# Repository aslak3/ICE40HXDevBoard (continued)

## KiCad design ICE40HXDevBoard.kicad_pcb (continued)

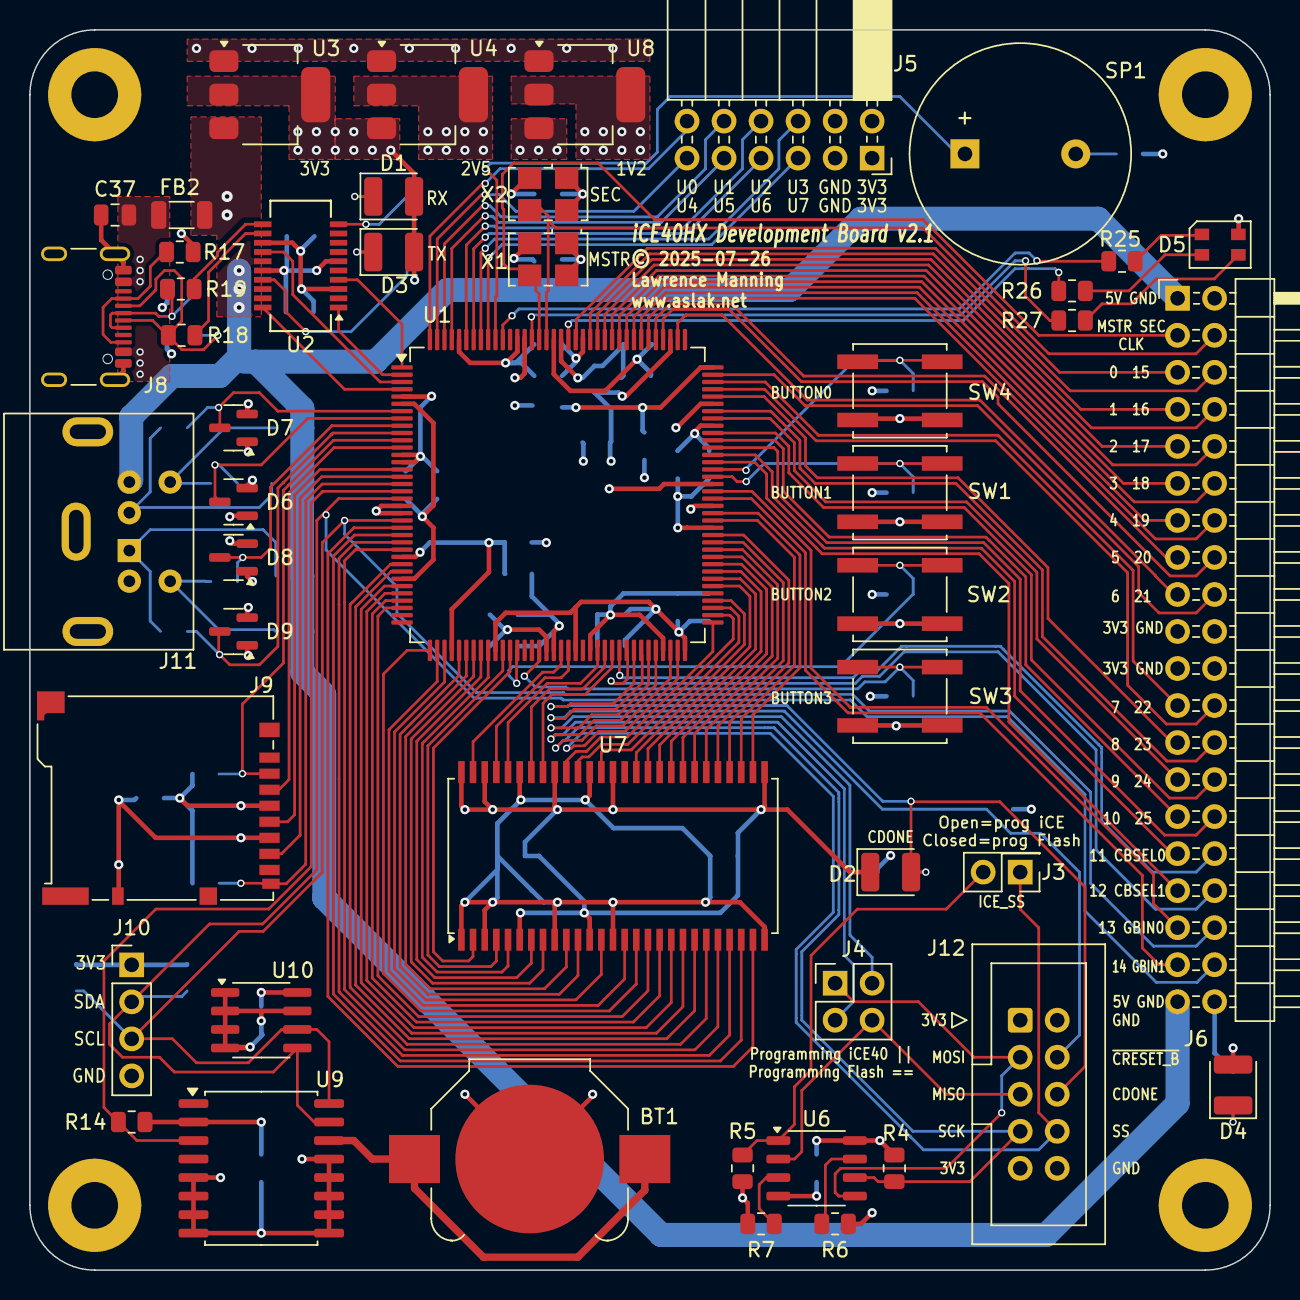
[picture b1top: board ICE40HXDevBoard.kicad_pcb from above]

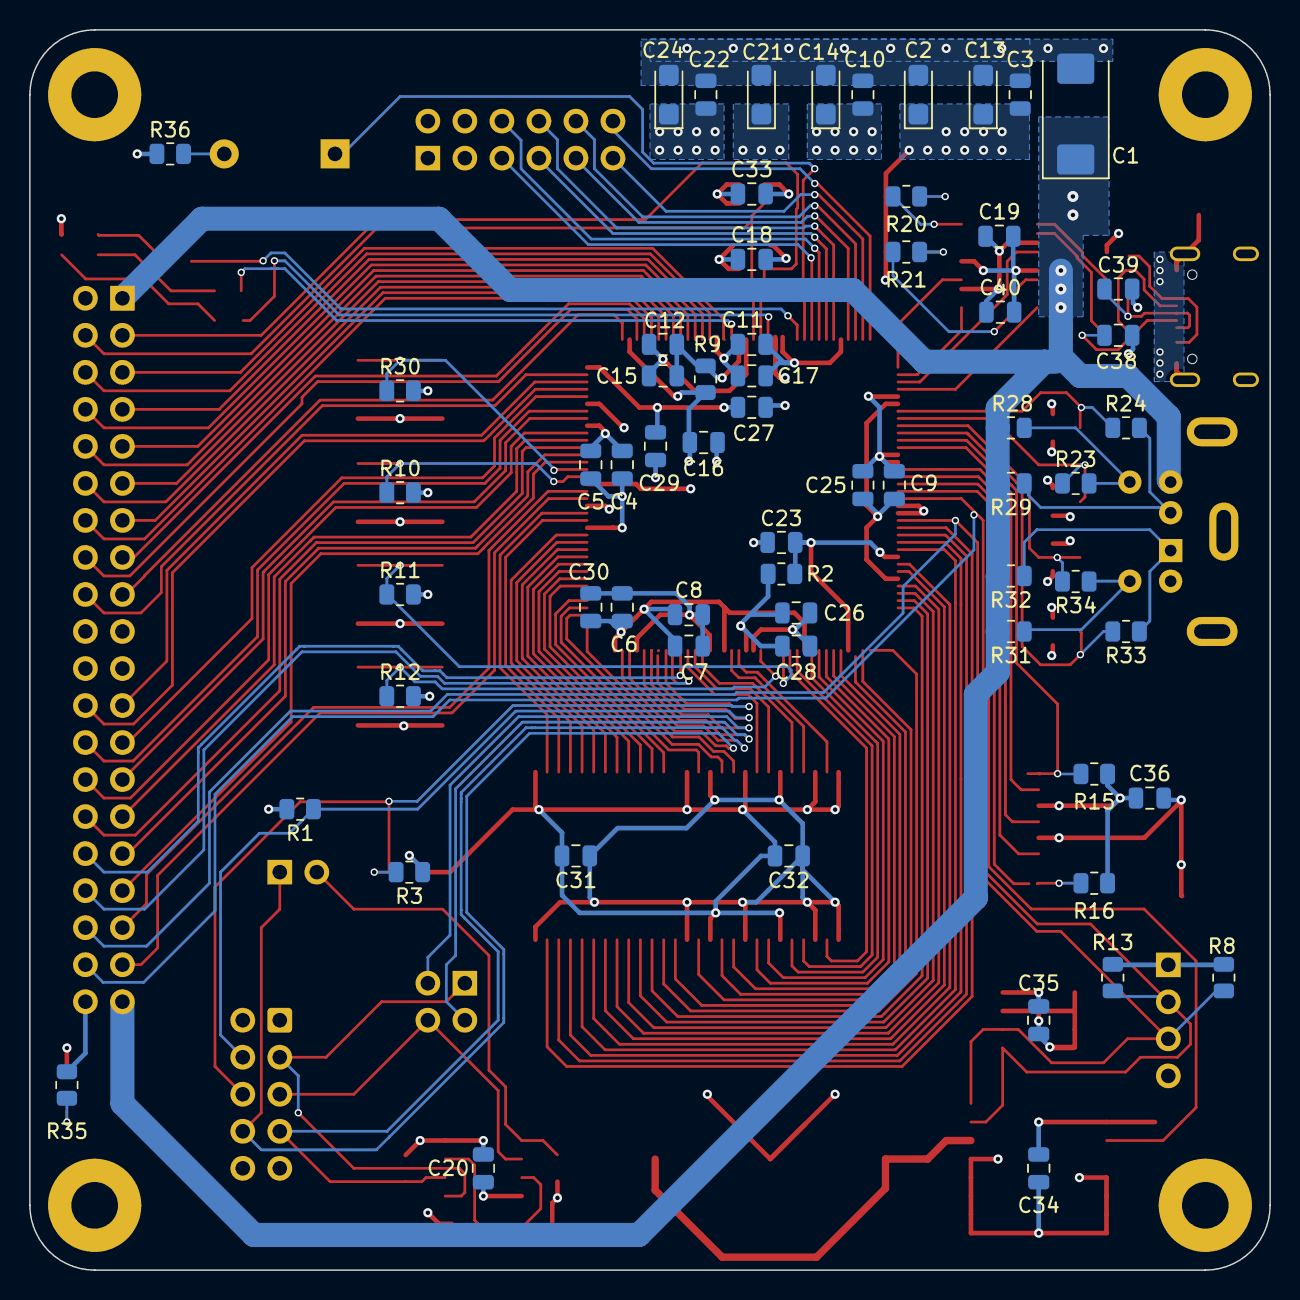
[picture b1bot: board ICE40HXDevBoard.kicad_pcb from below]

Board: 4 copper layers, 85.1 x 85.1 mm, 115 parts (63 on the bottom side), 141 nets.

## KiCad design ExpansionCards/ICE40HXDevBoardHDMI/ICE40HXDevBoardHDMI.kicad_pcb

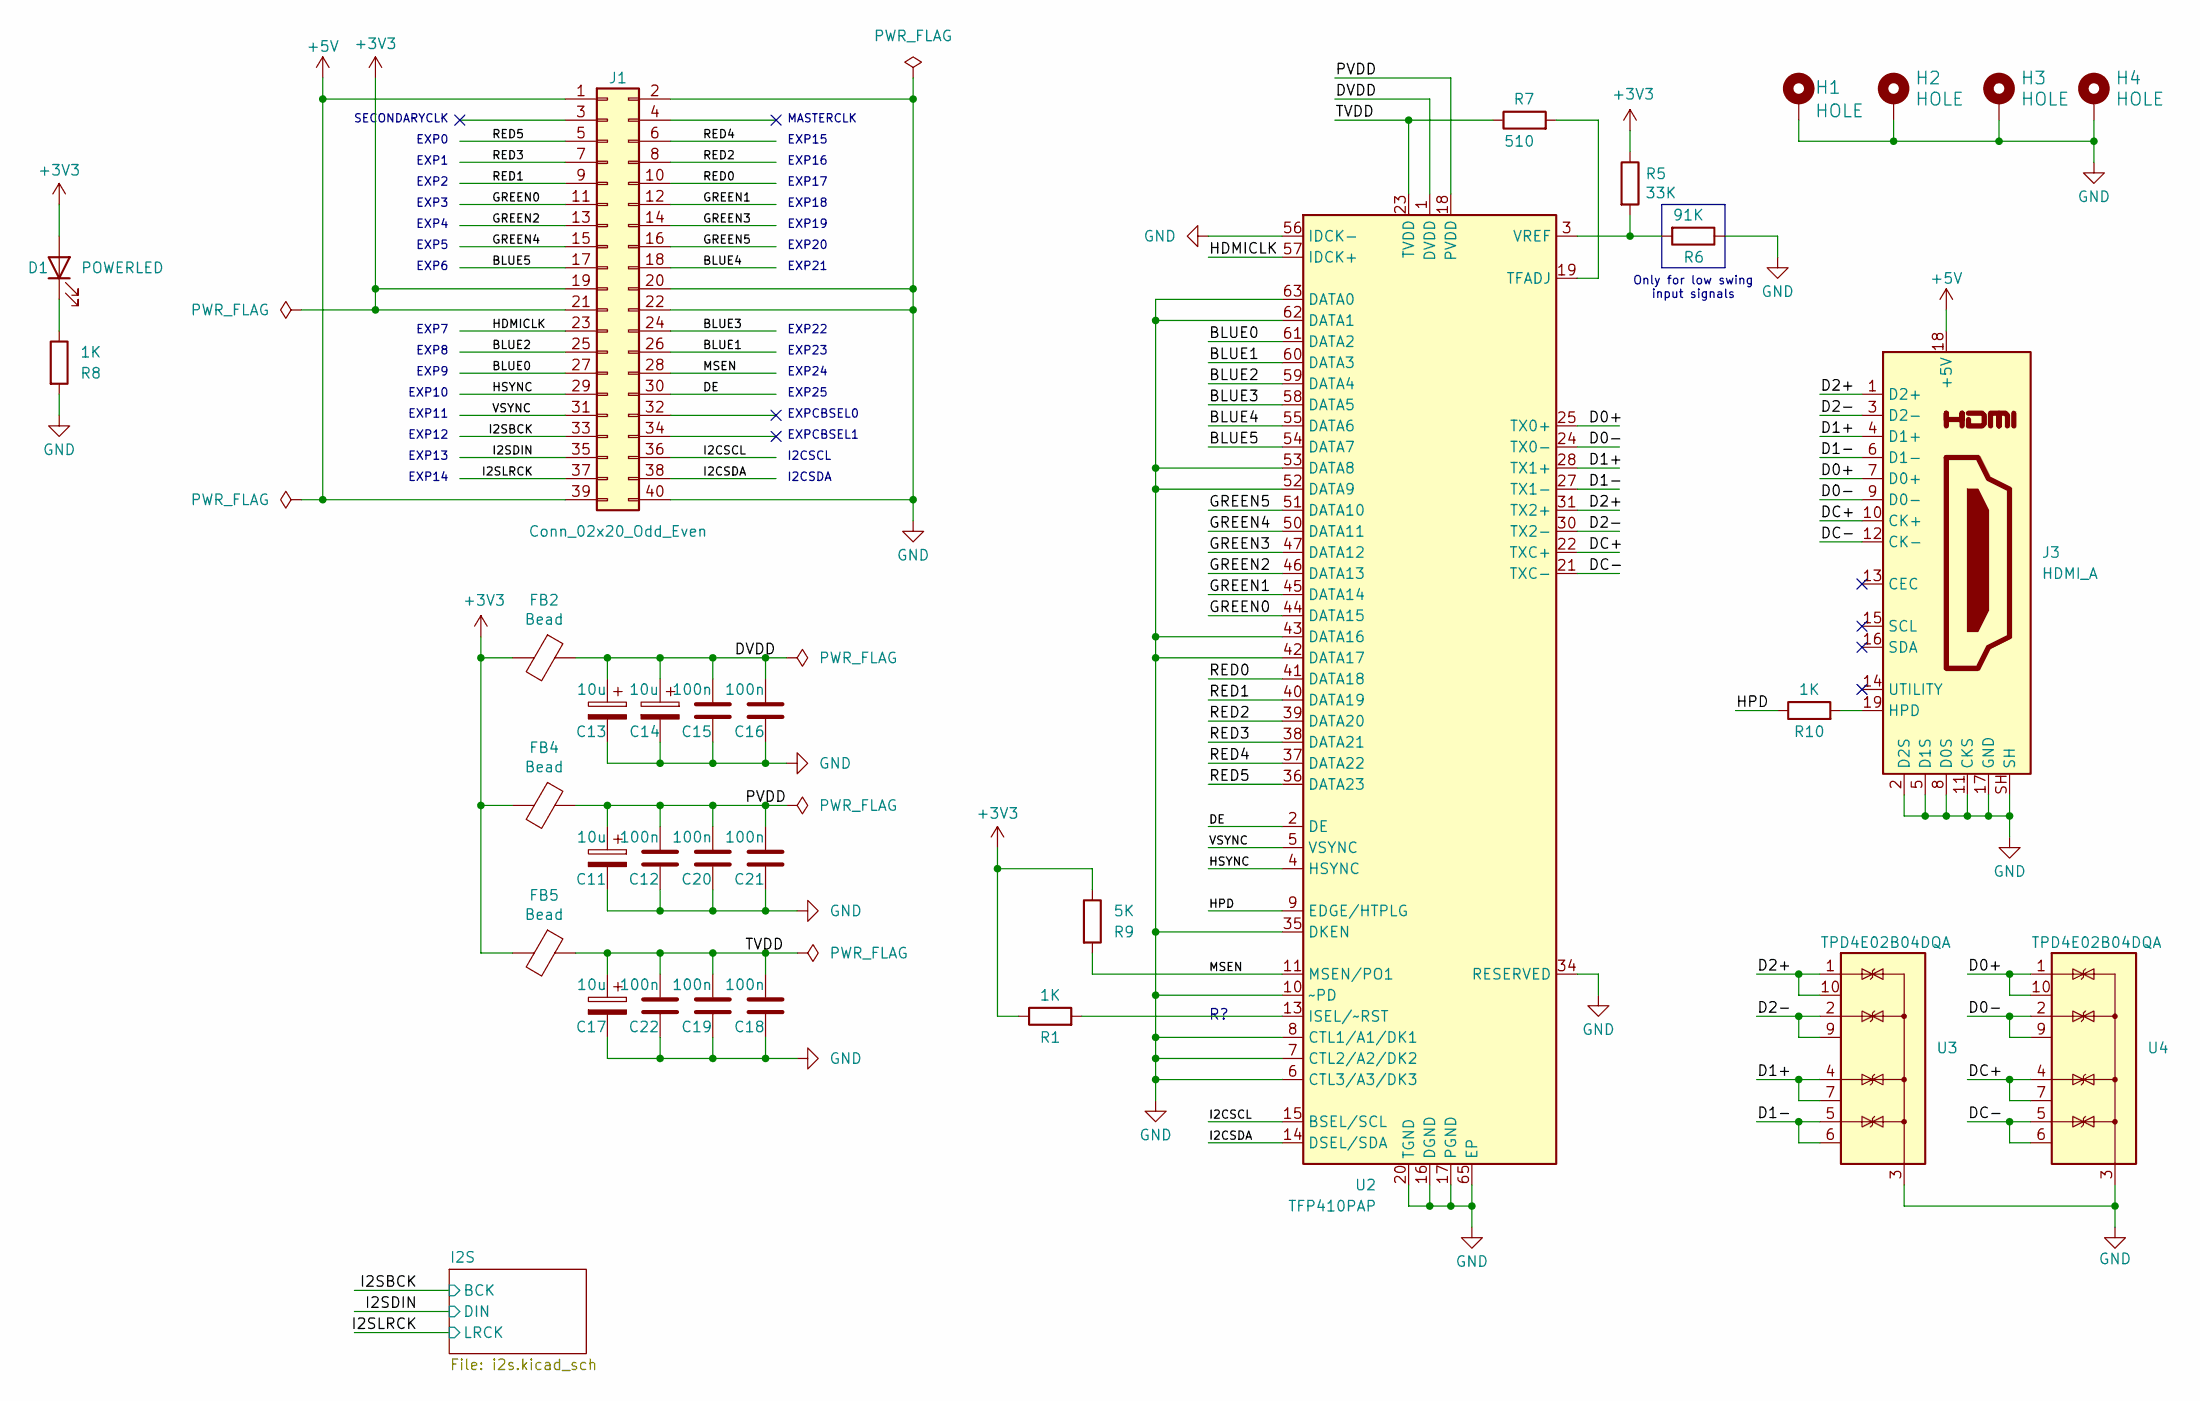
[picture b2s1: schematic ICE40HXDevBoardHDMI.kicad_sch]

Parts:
C11, C13, C14, C17: 10u; CP_EIA-3216-18_Kemet-A
C12, C15, C16, C18, C19, C20, C21, C22: 100n; C_0603_1608Metric
D1: POWERLED; LED_1210_3225Metric
FB2, FB4, FB5: Bead; L_0805_2012Metric
H1, H2, H3, H4: HOLE; MountingHole_3.2mm_M3_Pad
J1: Conn_02x20_Odd_Even; PinSocket_2x20_P2.54mm_Horizontal
J3: HDMI_A; HDMI_A_Molex_208658-1001_Horizontal
R1, R8, R10: 1K; R_0805_2012Metric
R5: 33K; R_0805_2012Metric
R6: 91K; R_0805_2012Metric
R7: 510; R_0805_2012Metric
R9: 5K; R_0805_2012Metric
U2: TFP410PAP; LQFP-64-1EP_10x10mm_P0.5mm_EP5x5mm_ThermalVias; MPN TFP410PAP; LCSC Part # C1543847
U3, U4: TPD4E02B04DQA; USON-10_2.5x1.0mm_P0.5mm

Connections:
+3V3: D1.2 (A), FB2.2, FB4.2, FB5.2, J1.19, J1.21, R1.1, R5.1, R9.1; also elsewhere on the board
+5V: J1.1, J1.39, J3.18 (+5V)
/BLUE0: J1.27, U2.61 (DATA2)
/BLUE1: J1.26, U2.60 (DATA3)
/BLUE2: J1.25, U2.59 (DATA4)
/BLUE3: J1.24, U2.58 (DATA5)
/BLUE4: J1.18, U2.55 (DATA6)
/BLUE5: J1.17, U2.54 (DATA7)
/D0+: J3.7 (D0+), U2.25 (TX0+), U4.1 (IO1), U4.10 (NC)
/D0-: J3.9 (D0-), U2.24 (TX0-), U4.2 (IO2), U4.9 (NC)
/D1+: J3.4 (D1+), U2.28 (TX1+), U3.4 (IO3), U3.7 (NC)
/D1-: J3.6 (D1-), U2.27 (TX1-), U3.5 (IO4), U3.6 (NC)
/D2+: J3.1 (D2+), U2.31 (TX2+), U3.1 (IO1), U3.10 (NC)
/D2-: J3.3 (D2-), U2.30 (TX2-), U3.2 (IO2), U3.9 (NC)
/DC+: J3.10 (CK+), U2.22 (TXC+), U4.4 (IO3), U4.7 (NC)
/DC-: J3.12 (CK-), U2.21 (TXC-), U4.5 (IO4), U4.6 (NC)
/DE: J1.30, U2.2 (DE)
/DVDD: C13.1, C14.1, C15.1, C16.1, FB2.1, U2.1 (DVDD), U2.12 (DVDD), U2.33 (DVDD)
/GREEN0: J1.11, U2.44 (DATA15)
/GREEN1: J1.12, U2.45 (DATA14)
/GREEN2: J1.13, U2.46 (DATA13)
/GREEN3: J1.14, U2.47 (DATA12)
/GREEN4: J1.15, U2.50 (DATA11)
/GREEN5: J1.16, U2.51 (DATA10)
/HDMICLK: J1.23, U2.57 (IDCK+)
/HPD: R10.1, U2.9 (EDGE/HTPLG)
/HSYNC: J1.29, U2.4 (HSYNC)
/I2CSCL: J1.36, U2.15 (BSEL/SCL)
/I2CSDA: J1.38, U2.14 (DSEL/SDA)
/I2SBCK: J1.33; also elsewhere on the board
/I2SDIN: J1.35; also elsewhere on the board
/I2SLRCK: J1.37; also elsewhere on the board
/MSEN: J1.28, R9.2, U2.11 (MSEN/PO1)
/PVDD: C11.1, C12.1, C20.1, C21.1, FB4.1, U2.18 (PVDD)
/RED0: J1.10, U2.41 (DATA18)
/RED1: J1.9, U2.40 (DATA19)
/RED2: J1.8, U2.39 (DATA20)
/RED3: J1.7, U2.38 (DATA21)
/RED4: J1.6, U2.37 (DATA22)
/RED5: J1.5, U2.36 (DATA23)
/TVDD: C17.1, C18.1, C19.1, C22.1, FB5.1, R7.1, U2.23 (TVDD), U2.29 (TVDD)
/VSYNC: J1.31, U2.5 (VSYNC)
GND: C11.2, C12.2, C13.2, C14.2, C15.2, C16.2, C17.2, C18.2, C19.2, C20.2, C21.2, C22.2, H1.1, H2.1, H3.1, H4.1, J1.2, J1.20, J1.22, J1.40, J3.2 (D2S), J3.5 (D1S), J3.8 (D0S), J3.11 (CKS), J3.17 (GND), J3.SH, R6.1, R8.2, U2.6 (CTL3/A3/DK3), U2.7 (CTL2/A2/DK2), U2.8 (CTL1/A1/DK1), U2.10 (~PD), U2.16 (DGND), U2.17 (PGND), U2.20 (TGND), U2.26 (TGND), U2.32 (TGND), U2.34 (RESERVED), U2.35 (DKEN), U2.42 (DATA17), U2.43 (DATA16), U2.48 (DGND), U2.52 (DATA9), U2.53 (DATA8), U2.56 (IDCK-), U2.62 (DATA1), U2.63 (DATA0), U2.64 (DGND), U2.65 (EP), U3.3 (G), U3.8 (G), U4.3 (G), U4.8 (G); also elsewhere on the board
unnamed: D1.1 (K), R8.1
unnamed: J3.19 (HPD), R10.2
unnamed: R1.2, U2.13 (ISEL/~RST)
unnamed: R7.2, U2.19 (TFADJ)
unnamed: R5.2, R6.2, U2.3 (VREF)

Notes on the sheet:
EXP13
EXP8
EXP24
EXP16
EXP4
EXP3
EXP14
EXP20
EXP23
EXP22
EXP5
Only for low swing input signals
EXP1
I2CSDA
EXP6
EXP2
EXP0
SECONDARYCLK
EXP25
MASTERCLK
EXP11
EXP9
EXP10
EXPCBSEL0
EXP15
EXP17
EXP19
EXPCBSEL1
EXP7
I2CSCL
EXP12
EXP18
EXP21

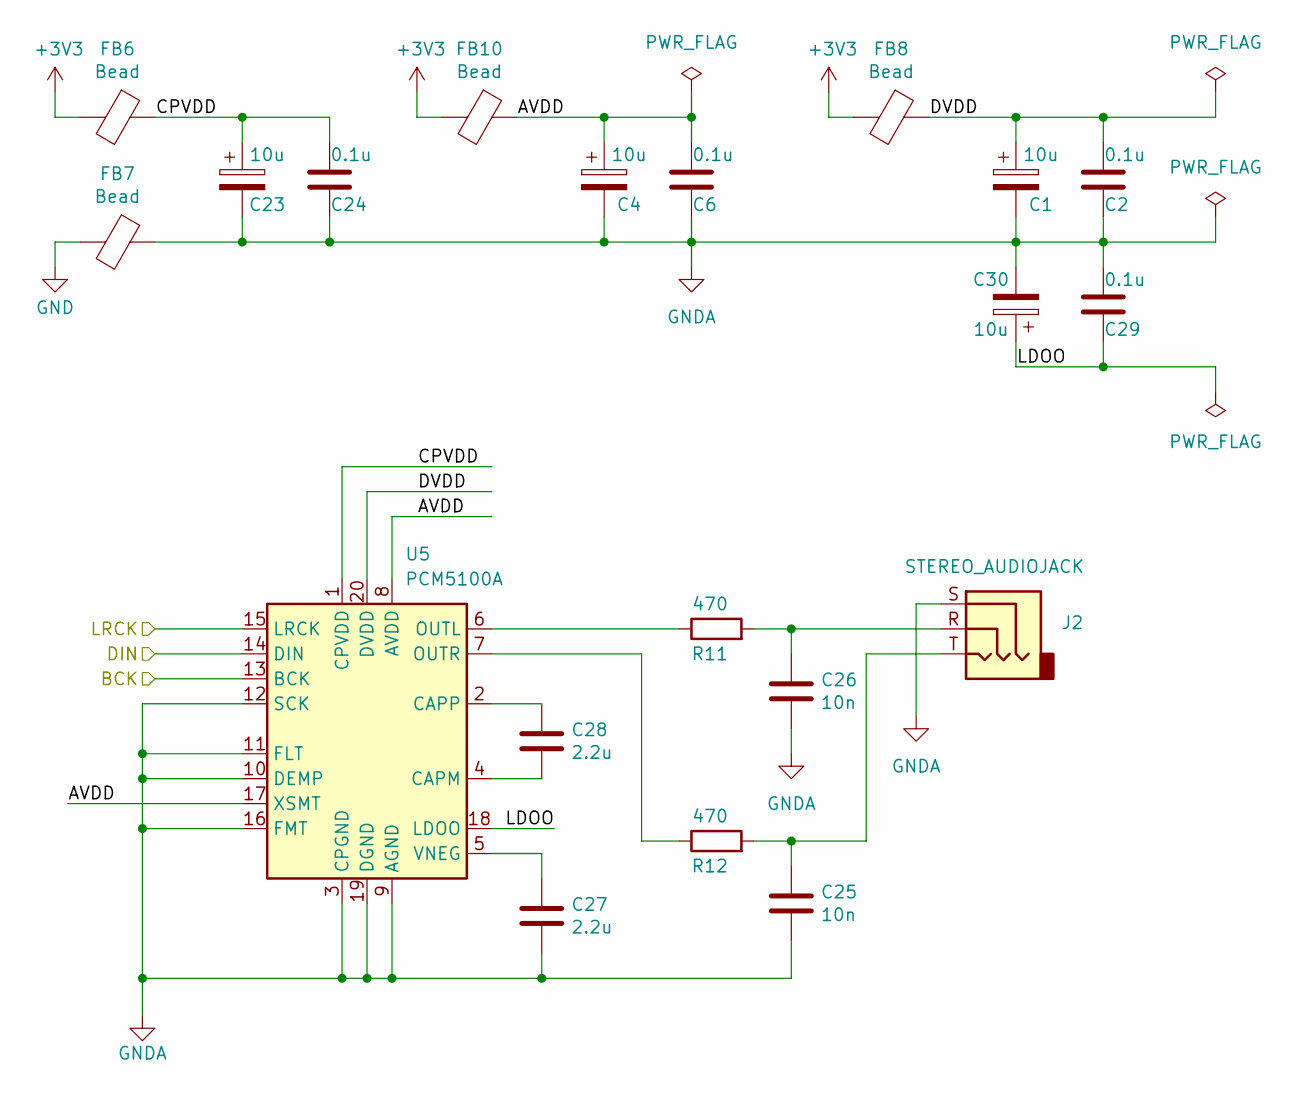
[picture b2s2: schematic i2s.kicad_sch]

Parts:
C1, C4, C23, C30: 10u; CP_EIA-3216-18_Kemet-A
C2, C6, C24, C29: 0.1u; C_0805_2012Metric
C25, C26: 10n; C_0805_2012Metric
C27, C28: 2.2u; C_0805_2012Metric
FB6, FB7, FB8, FB10: Bead; L_1206_3216Metric
J2: STEREO_AUDIOJACK; Jack_3.5mm_Switronic_ST-005-G_horizontal
R11, R12: 470; R_0805_2012Metric
U5: PCM5100A; TSSOP-20_4.4x6.5mm_P0.65mm

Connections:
+3V3: FB6.2, FB8.2, FB10.2; also elsewhere on the board
/I2S/AVDD: C4.1, C6.1, FB10.1, U5.8 (AVDD), U5.17 (XSMT)
/I2S/CPVDD: C23.1, C24.1, FB6.1, U5.1 (CPVDD)
/I2S/DVDD: C1.1, C2.1, FB8.1, U5.20 (DVDD)
/I2S/LDOO: C29.2, C30.1, U5.18 (LDOO)
/I2SBCK: U5.13 (BCK); also elsewhere on the board
/I2SDIN: U5.14 (DIN); also elsewhere on the board
/I2SLRCK: U5.15 (LRCK); also elsewhere on the board
GND: FB7.2; also elsewhere on the board
GNDA: C1.2, C2.2, C4.2, C6.2, C23.2, C24.2, C25.2, C26.2, C27.2, C29.1, C30.2, FB7.1, J2.S, U5.3 (CPGND), U5.9 (AGND), U5.10 (DEMP), U5.11 (FLT), U5.12 (SCK), U5.16 (FMT), U5.19 (DGND)
unnamed: C25.1, J2.T, R12.2
unnamed: C26.1, J2.R, R11.2
unnamed: C28.2, U5.4 (CAPM)
unnamed: C28.1, U5.2 (CAPP)
unnamed: R11.1, U5.6 (OUTL)
unnamed: R12.1, U5.7 (OUTR)
unnamed: C27.1, U5.5 (VNEG)

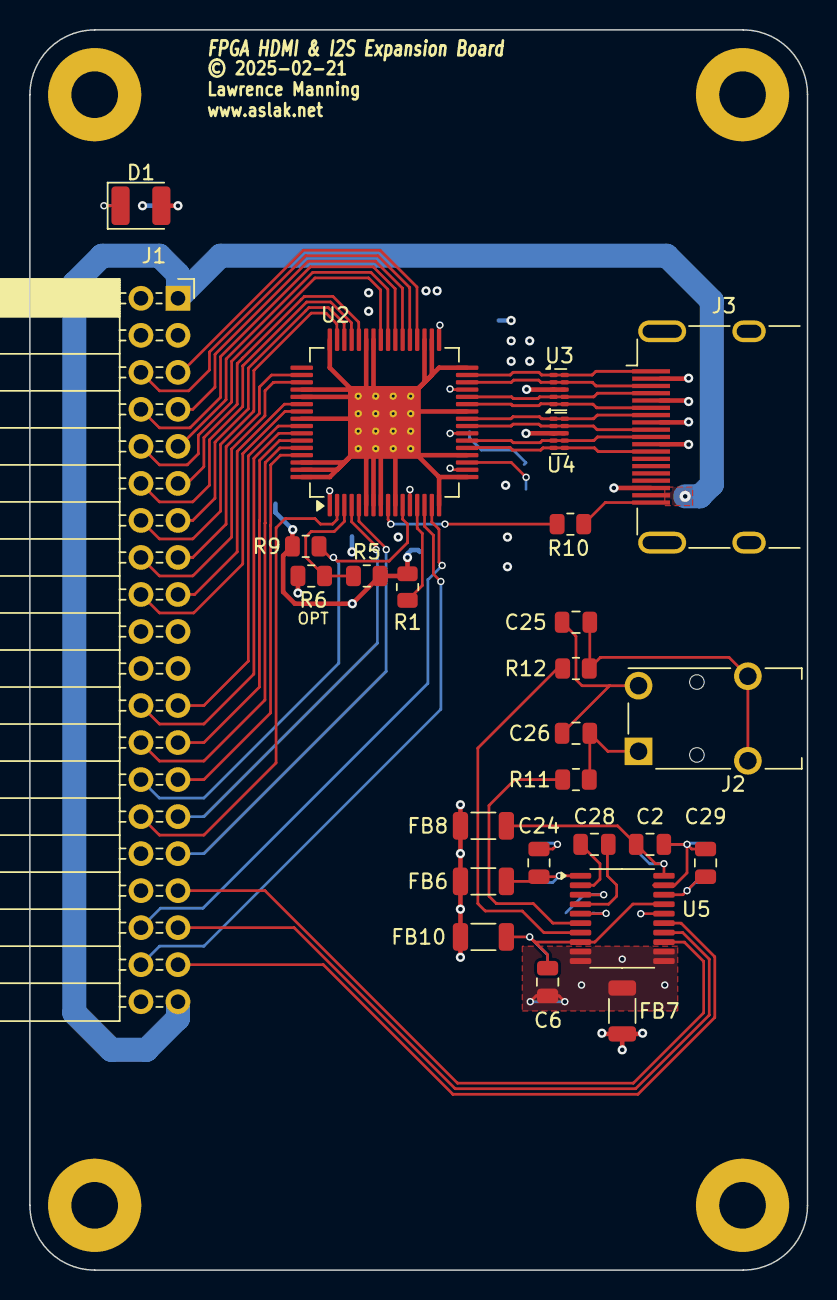
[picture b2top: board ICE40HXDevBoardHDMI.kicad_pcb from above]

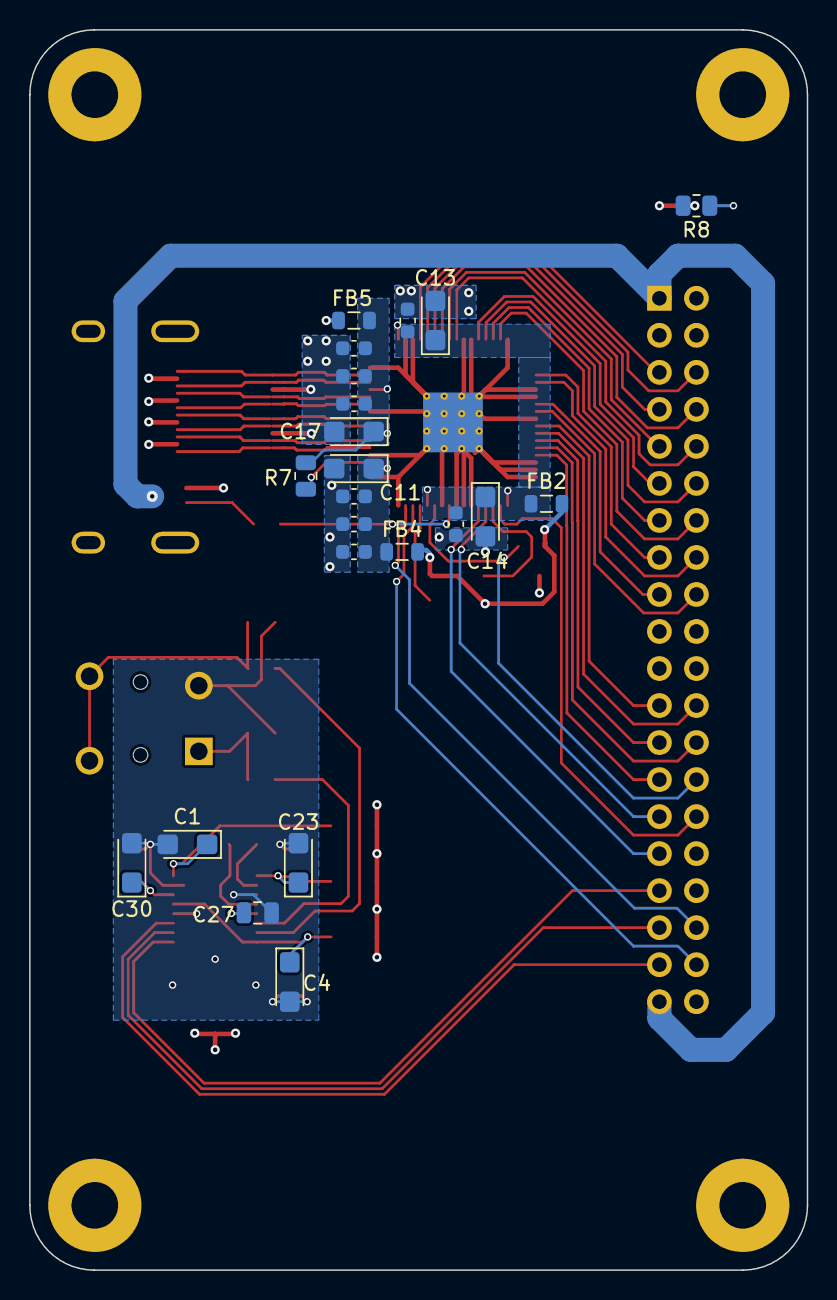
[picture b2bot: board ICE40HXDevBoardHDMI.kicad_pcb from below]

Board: 4 copper layers, 53.4 x 85.1 mm, 52 parts (22 on the bottom side), 60 nets.

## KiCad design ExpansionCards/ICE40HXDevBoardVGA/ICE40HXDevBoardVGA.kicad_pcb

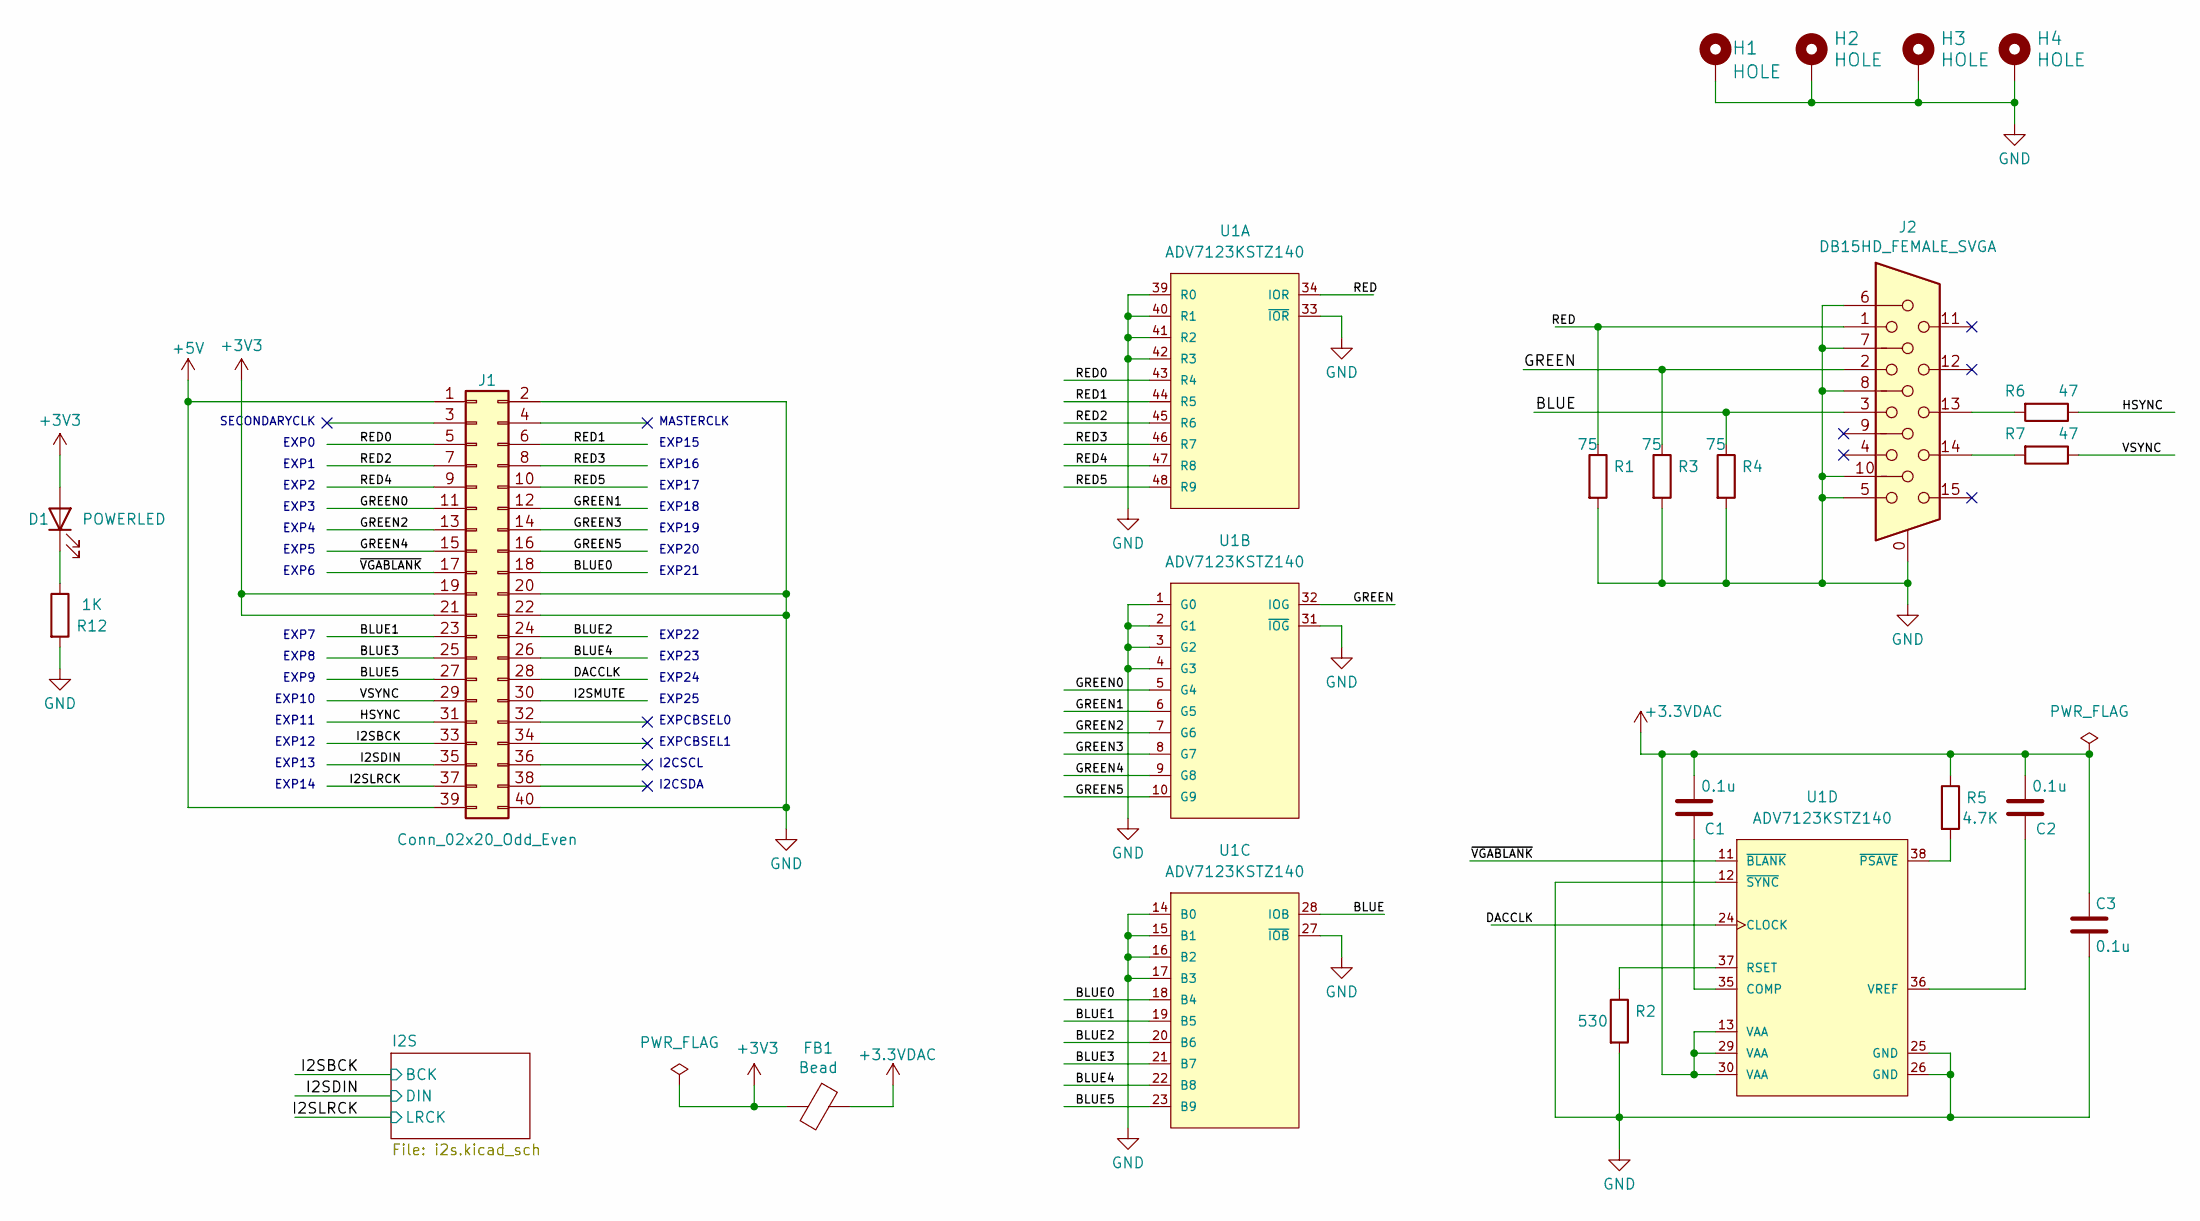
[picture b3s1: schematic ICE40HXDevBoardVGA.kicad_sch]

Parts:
C1, C2, C3: 0.1u; C_0805_2012Metric
D1: POWERLED; LED_1210_3225Metric
FB1: Bead; L_1206_3216Metric
H1, H2, H3, H4: HOLE; MountingHole_3.2mm_M3_Pad
J1: Conn_02x20_Odd_Even; PinSocket_2x20_P2.54mm_Horizontal
J2: DB15HD_FEMALE_SVGA; DSUB-15-HD_Female_Horizontal_P2.29x1.90mm_EdgePinOffset3.03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
R1, R3, R4: 75; R_0805_2012Metric
R2: 530; R_0805_2012Metric
R5: 4.7K; R_0805_2012Metric
R6, R7: 47; R_0805_2012Metric
R12: 1K; R_0805_2012Metric
U1: ADV7123KSTZ140; LQFP-48_7x7mm_P0.5mm

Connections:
+3.3VDAC: C1.2, C2.2, C3.1, FB1.1, R5.1, U1.13 (VAA), U1.29 (VAA), U1.30 (VAA)
+3V3: D1.2 (A), FB1.2, J1.19, J1.21; also elsewhere on the board
+5V: J1.1, J1.39
/BLUE: J2.3, R4.1, U1.28 (IOB)
/BLUE0: J1.18, U1.18 (B4)
/BLUE1: J1.23, U1.19 (B5)
/BLUE2: J1.24, U1.20 (B6)
/BLUE3: J1.25, U1.21 (B7)
/BLUE4: J1.26, U1.22 (B8)
/BLUE5: J1.27, U1.23 (B9)
/DACCLK: J1.28, U1.24 (CLOCK)
/GREEN: J2.2, R3.1, U1.32 (IOG)
/GREEN0: J1.11, U1.5 (G4)
/GREEN1: J1.12, U1.6 (G5)
/GREEN2: J1.13, U1.7 (G6)
/GREEN3: J1.14, U1.8 (G7)
/GREEN4: J1.15, U1.9 (G8)
/GREEN5: J1.16, U1.10 (G9)
/HSYNC: J1.31, R6.1
/I2SBCK: J1.33; also elsewhere on the board
/I2SDIN: J1.35; also elsewhere on the board
/I2SLRCK: J1.37; also elsewhere on the board
/I2SMUTE: J1.30
/RED: J2.1, R1.1, U1.34 (IOR)
/RED0: J1.5, U1.43 (R4)
/RED1: J1.6, U1.44 (R5)
/RED2: J1.7, U1.45 (R6)
/RED3: J1.8, U1.46 (R7)
/RED4: J1.9, U1.47 (R8)
/RED5: J1.10, U1.48 (R9)
/VSYNC: J1.29, R7.1
/~VGABLANK: J1.17, U1.11 (~BLANK)
GND: C3.2, H1.1, H2.1, H3.1, H4.1, J1.2, J1.20, J1.22, J1.40, J2.0, J2.5, J2.6, J2.7, J2.8, J2.10, R1.2, R2.2, R3.2, R4.2, R12.2, U1.1 (G0), U1.2 (G1), U1.3 (G2), U1.4 (G3), U1.12 (~SYNC), U1.14 (B0), U1.15 (B1), U1.16 (B2), U1.17 (B3), U1.25 (GND), U1.26 (GND), U1.27 (~IOB), U1.31 (~IOG), U1.33 (~IOR), U1.39 (R0), U1.40 (R1), U1.41 (R2), U1.42 (R3); also elsewhere on the board
unnamed: D1.1 (K), R12.1
unnamed: J2.13, R6.2
unnamed: J2.14, R7.2
unnamed: C1.1, U1.35 (COMP)
unnamed: R2.1, U1.37 (RSET)
unnamed: C2.1, U1.36 (VREF)
unnamed: R5.2, U1.38 (~PSAVE)

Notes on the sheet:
EXP13
EXP8
EXP24
EXP16
EXP4
EXP3
EXP14
EXP20
EXP23
EXP22
EXP5
EXP1
I2CSDA
EXP6
EXP2
EXP0
SECONDARYCLK
EXP25
MASTERCLK
EXP11
EXP9
EXP10
EXPCBSEL0
EXP15
EXP17
EXP19
EXPCBSEL1
EXP7
I2CSCL
EXP12
EXP18
EXP21

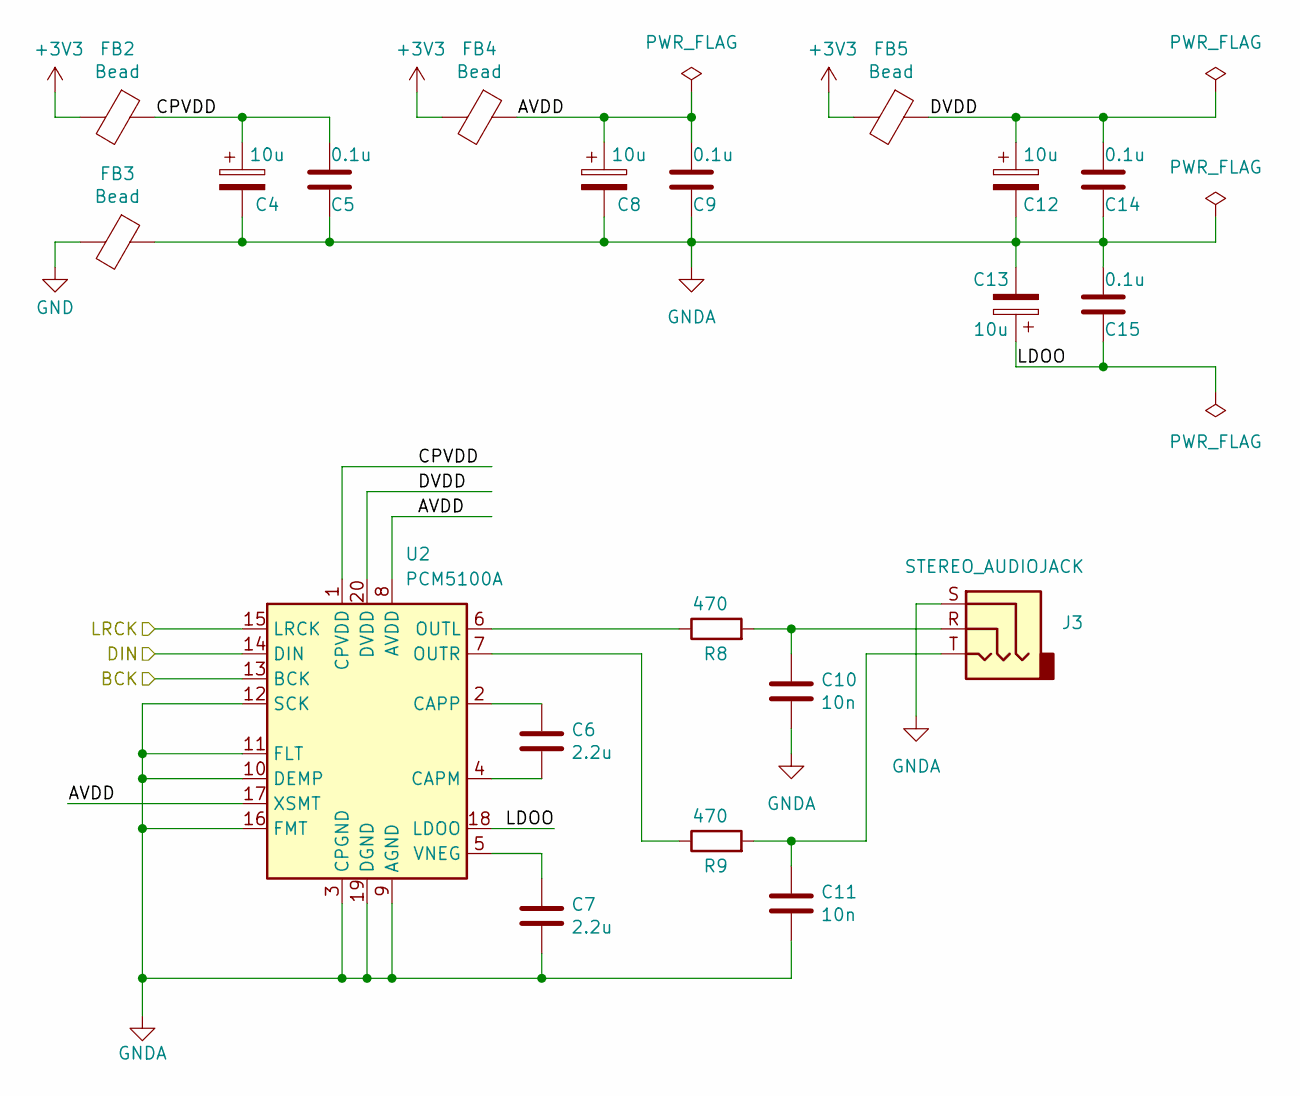
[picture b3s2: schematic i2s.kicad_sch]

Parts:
C4, C8, C12, C13: 10u; CP_EIA-3216-18_Kemet-A
C5, C9, C14, C15: 0.1u; C_0805_2012Metric
C6, C7: 2.2u; C_0805_2012Metric
C10, C11: 10n; C_0805_2012Metric
FB2, FB3, FB4, FB5: Bead; L_1206_3216Metric
J3: STEREO_AUDIOJACK; Jack_3.5mm_Switronic_ST-005-G_horizontal
R8, R9: 470; R_0805_2012Metric
U2: PCM5100A; TSSOP-20_4.4x6.5mm_P0.65mm

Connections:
+3V3: FB2.2, FB4.2, FB5.2; also elsewhere on the board
/I2S/AVDD: C8.1, C9.1, FB4.1, U2.8 (AVDD), U2.17 (XSMT)
/I2S/CPVDD: C4.1, C5.1, FB2.1, U2.1 (CPVDD)
/I2S/DVDD: C12.1, C14.1, FB5.1, U2.20 (DVDD)
/I2S/LDOO: C13.1, C15.2, U2.18 (LDOO)
/I2SBCK: U2.13 (BCK); also elsewhere on the board
/I2SDIN: U2.14 (DIN); also elsewhere on the board
/I2SLRCK: U2.15 (LRCK); also elsewhere on the board
GND: FB3.2; also elsewhere on the board
GNDA: C4.2, C5.2, C7.2, C8.2, C9.2, C10.2, C11.2, C12.2, C13.2, C14.2, C15.1, FB3.1, J3.S, U2.3 (CPGND), U2.9 (AGND), U2.10 (DEMP), U2.11 (FLT), U2.12 (SCK), U2.16 (FMT), U2.19 (DGND)
unnamed: C10.1, J3.R, R8.2
unnamed: C11.1, J3.T, R9.2
unnamed: C6.2, U2.4 (CAPM)
unnamed: C6.1, U2.2 (CAPP)
unnamed: R8.1, U2.6 (OUTL)
unnamed: R9.1, U2.7 (OUTR)
unnamed: C7.1, U2.5 (VNEG)

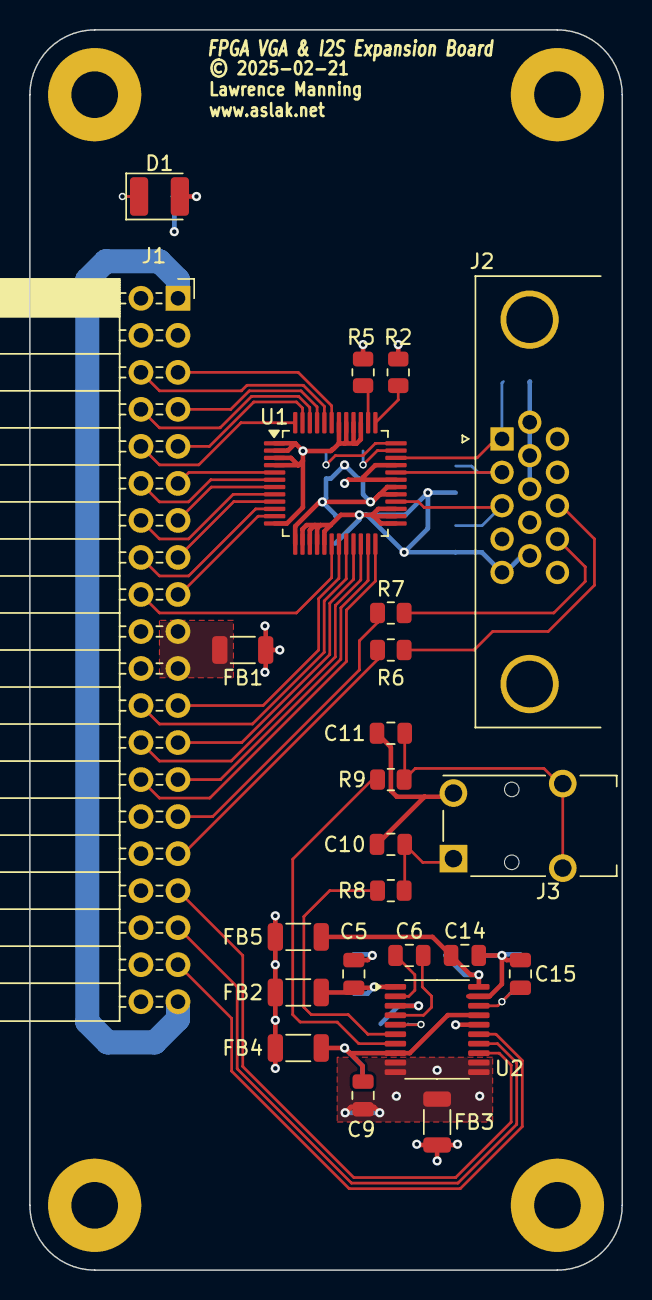
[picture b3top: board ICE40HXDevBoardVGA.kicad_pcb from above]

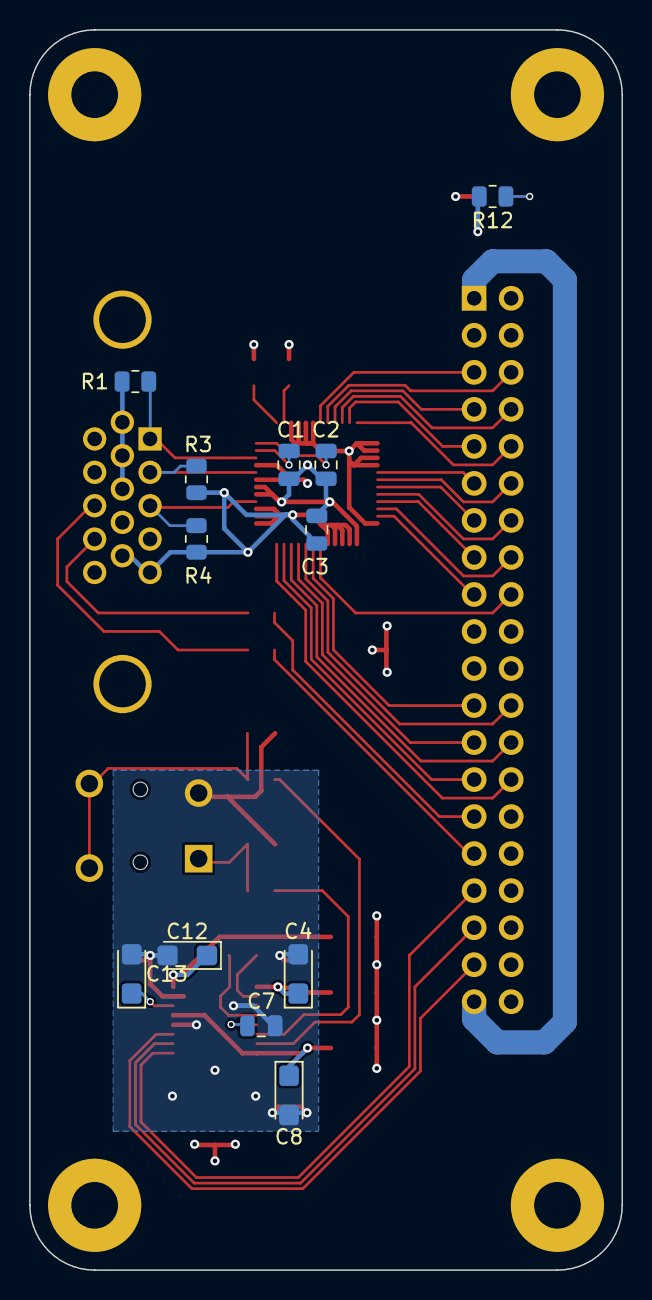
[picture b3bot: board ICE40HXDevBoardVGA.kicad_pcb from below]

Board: 4 copper layers, 40.6 x 85.1 mm, 40 parts (12 on the bottom side), 51 nets.
